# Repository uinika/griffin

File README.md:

# griffin
an evaluation PCB board with multicore CH340E ESP32 STM32 STC89C52.

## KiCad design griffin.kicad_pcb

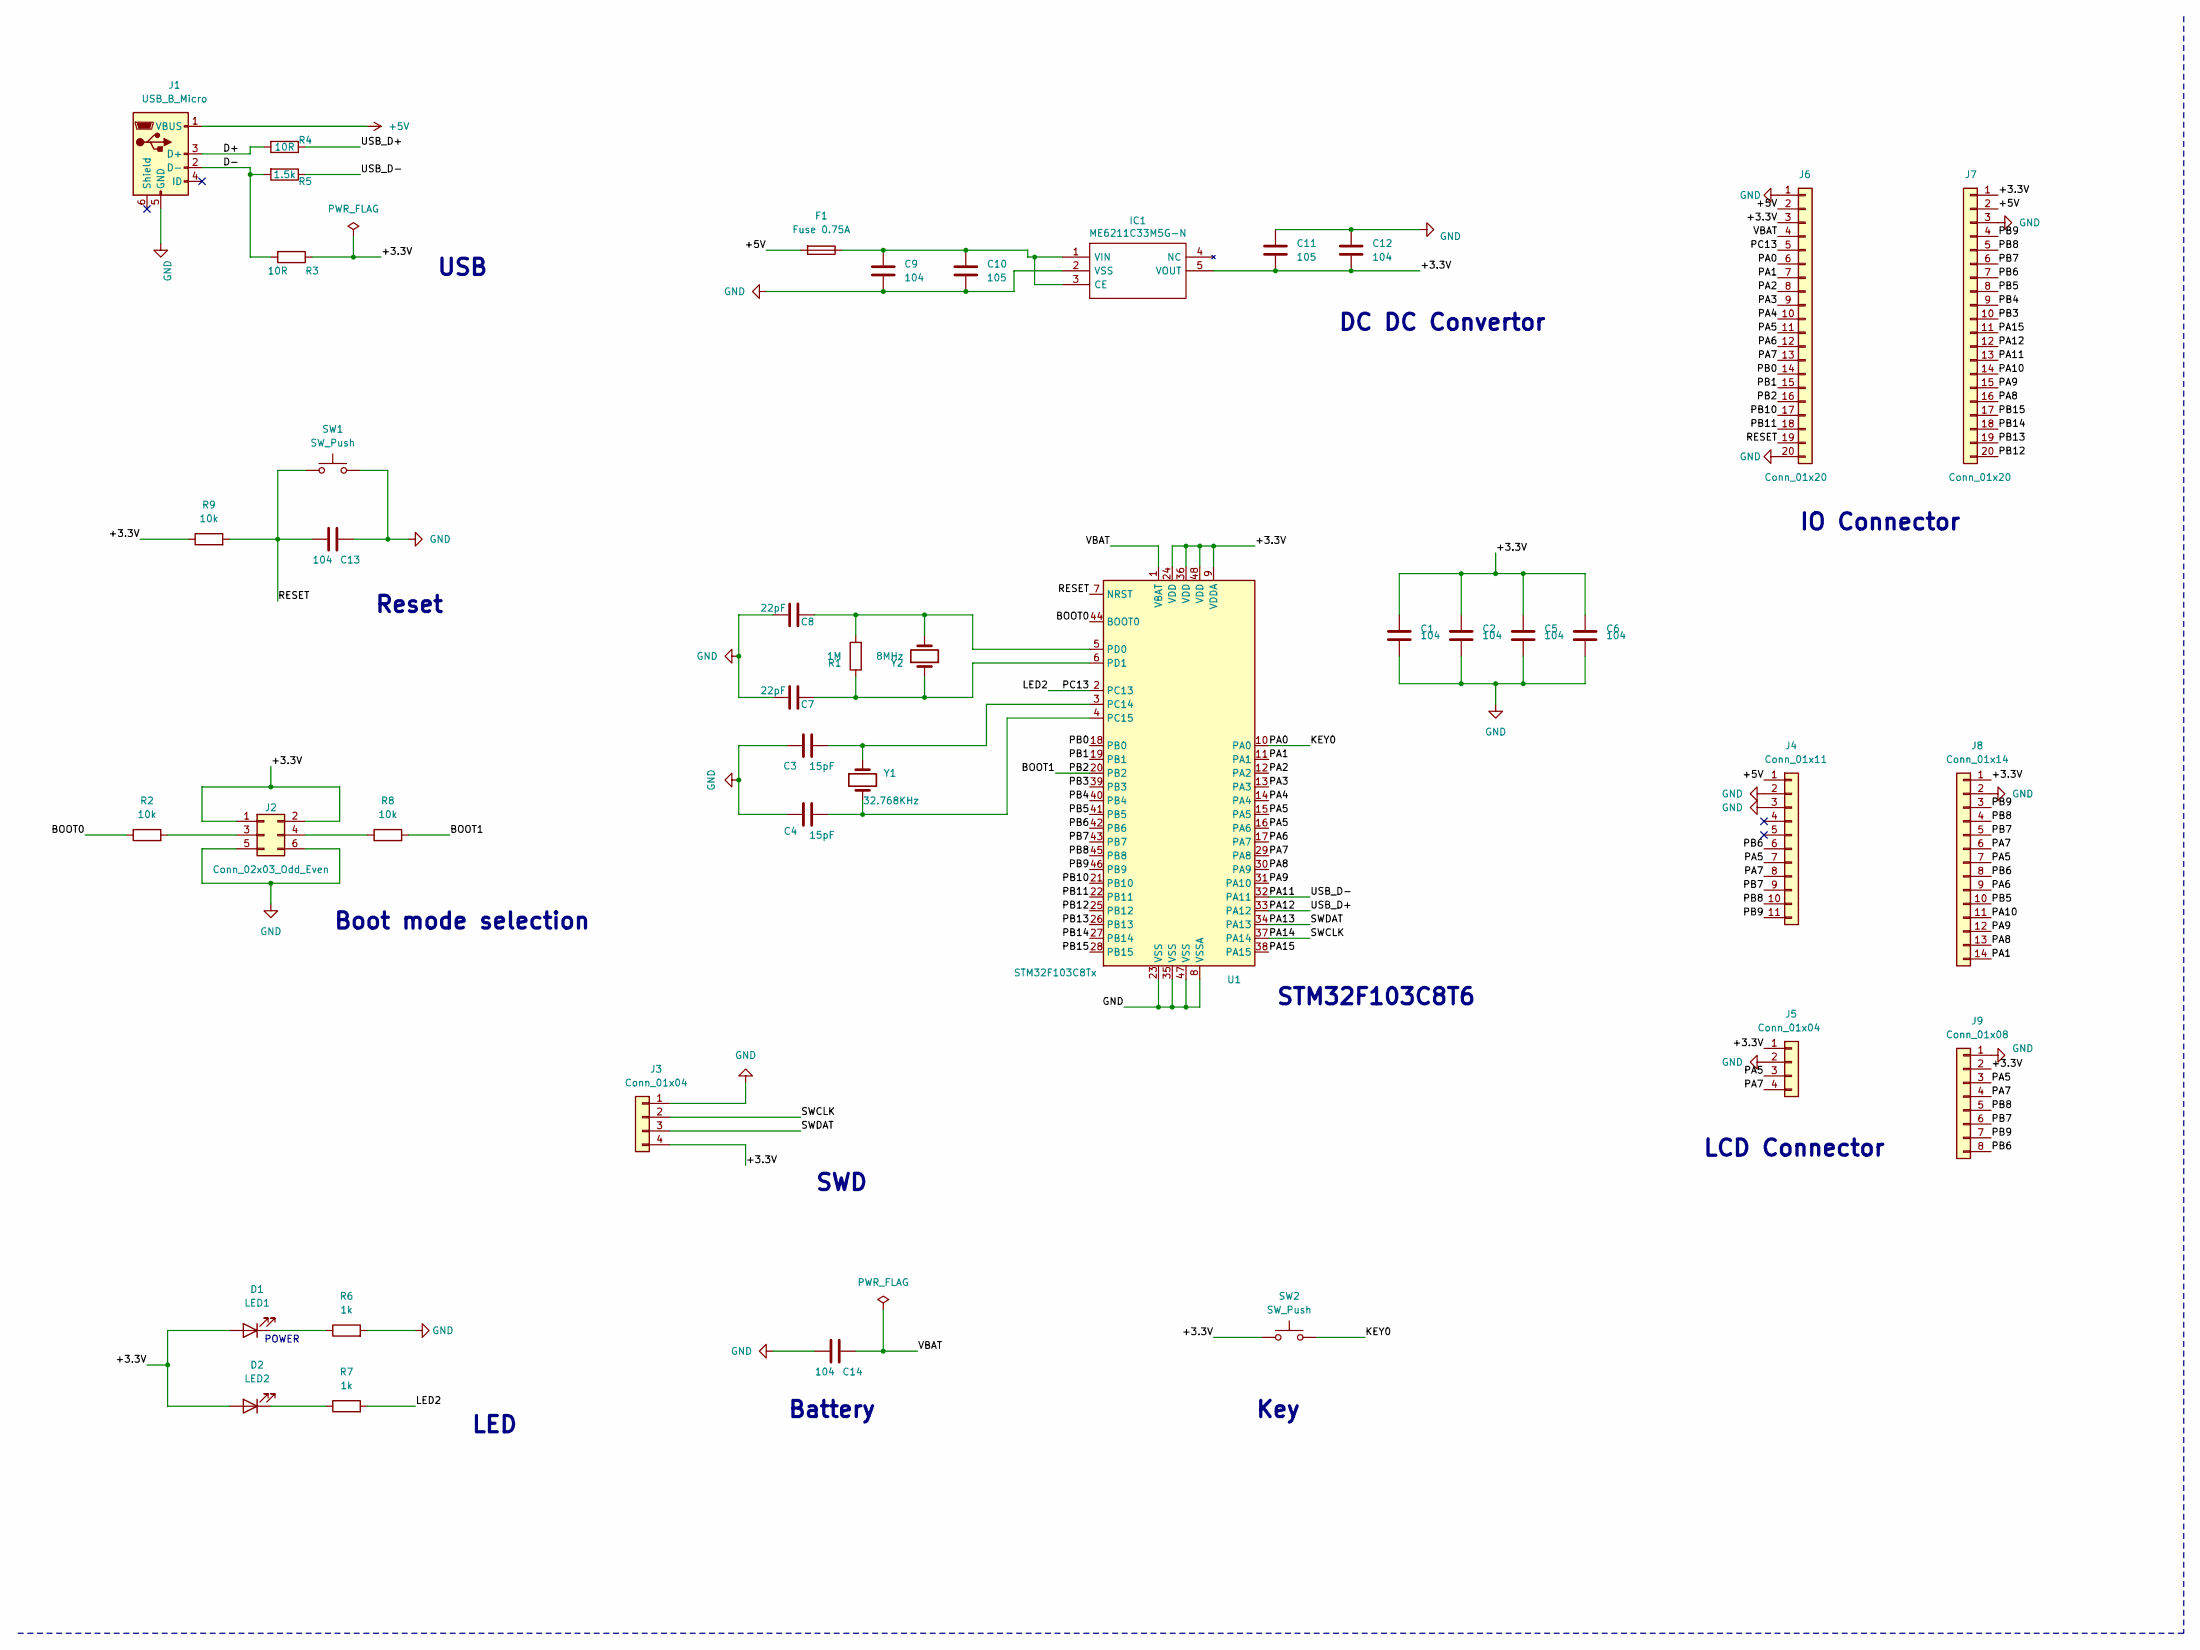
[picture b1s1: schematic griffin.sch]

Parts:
C1, C2, C5, C6, C9, C12, C13, C14: 104; C_0603_1608Metric
C3, C4: 15pF; C_0603_1608Metric
C7, C8: 22pF; C_0603_1608Metric
C10, C11: 105; C_0603_1608Metric
D1: LED1; LED_0805_2012Metric
D2: LED2; LED_0805_2012Metric
F1: Fuse 0.75A; Fuse_0805_2012Metric
IC1: ME6211C33M5G-N; SOT95P270X145-5N; Manufacturer_Part_Number ME6211C33M5G-N
J1: USB_B_Micro; USB_Micro-B_Molex-105017-0001
J2: Conn_02x03_Odd_Even; PinHeader_2x03_P2.54mm_Vertical
J3: Conn_01x04; PinSocket_1x04_P2.54mm_Vertical
J4: Conn_01x11; PinSocket_1x11_P2.54mm_Vertical
J5: Conn_01x04; PinHeader_1x04_P2.54mm_Vertical
J6, J7: Conn_01x20; PinHeader_1x20_P2.54mm_Vertical
J8: Conn_01x14; PinSocket_1x14_P2.54mm_Vertical
J9: Conn_01x08; PinSocket_1x08_P2.54mm_Vertical
R1: 1M; R_0603_1608Metric
R2, R8, R9: 10k; R_0603_1608Metric
R3, R4: 10R; R_0603_1608Metric
R5: 1.5k; R_0603_1608Metric
R6, R7: 1k; R_0603_1608Metric
SW1, SW2: SW_Push; SW_PUSH_6mm
U1: STM32F103C8Tx; LQFP-48_7x7mm_P0.5mm
Y1: 32.768KHz; Crystal_SMD_3215-2Pin_3.2x1.5mm
Y2: 8MHz; Crystal_HC18-U_Vertical

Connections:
+5V: F1.2, J1.1 (VBUS), J4.1, J6.2, J7.2
/+3.3V: C1.2, C2.2, C5.2, C6.2, C11.2, C12.2, D1.2 (A), D2.2 (A), IC1.5 (VOUT), J2.1, J2.2, J3.4, J5.1, J6.3, J7.1, J8.1, J9.2, R3.1, R9.1, SW2.1, U1.9 (VDDA), U1.24 (VDD), U1.36 (VDD), U1.48 (VDD)
/BOOT0: R2.1, U1.44 (BOOT0)
/BOOT1: J6.16, R8.2, U1.20 (PB2)
/D+: J1.3 (D+), R4.2
/D-: J1.2 (D-), R3.2, R5.2
/KEY0: J6.6, SW2.2, U1.10 (PA0)
/LED2: J6.5, R7.2, U1.2 (PC13)
/PA1: J6.7, J8.14, U1.11 (PA1)
/PA2: J6.8, U1.12 (PA2)
/PA3: J6.9, U1.13 (PA3)
/PA4: J6.10, U1.14 (PA4)
/PA5: J4.7, J5.3, J6.11, J8.7, J9.3, U1.15 (PA5), U1.16 (PA6)
/PA6: J6.12, J8.9, U1.17 (PA7)
/PA7: J4.8, J5.4, J6.13, J8.6, J9.4, U1.29 (PA8)
/PA8: J7.16, J8.13, U1.30 (PA9)
/PA9: J7.15, J8.12, U1.31 (PA10)
/PA10: J7.14, J8.11
/PA11: J7.13, R5.1, U1.32 (PA11)
/PA12: J7.12, R4.1, U1.33 (PA12)
/PA13: J3.3, U1.34 (PA13)
/PA14: J3.2, U1.37 (PA14)
/PA15: J7.11, U1.38 (PA15)
/PB0: J6.14, U1.18 (PB0)
/PB1: J6.15, U1.19 (PB1)
/PB3: J7.10, U1.39 (PB3)
/PB4: J7.9, U1.40 (PB4)
/PB5: J7.8, J8.10, U1.41 (PB5)
/PB6: J4.6, J7.7, J8.8, J9.8, U1.42 (PB6)
/PB7: J4.9, J7.6, J8.5, J9.6, U1.43 (PB7)
/PB8: J4.10, J7.5, J8.4, J9.5, U1.45 (PB8)
/PB9: J4.11, J7.4, J8.3, J9.7, U1.46 (PB9)
/PB10: J6.17, U1.21 (PB10)
/PB11: J6.18, U1.22 (PB11)
/PB12: J7.20, U1.25 (PB12)
/PB13: J7.19, U1.26 (PB13)
/PB14: J7.18, U1.27 (PB14)
/PB15: J7.17, U1.28 (PB15)
/RESET: C13.2, J6.19, R9.2, SW1.1, U1.7 (NRST)
/VBAT: C14.1, J6.4, U1.1 (VBAT)
GND: C1.1, C2.1, C3.1, C4.1, C5.1, C6.1, C7.1, C8.1, C9.2, C10.2, C11.1, C12.1, C13.1, C14.2, IC1.2 (VSS), J1.5 (GND), J2.5, J2.6, J3.1, J4.2, J4.3, J5.2, J6.1, J6.20, J7.3, J8.2, J9.1, R6.2, SW1.2, U1.8 (VSSA), U1.23 (VSS), U1.35 (VSS), U1.47 (VSS)
unnamed: C3.2, U1.3 (PC14), Y1.1
unnamed: C4.2, U1.4 (PC15), Y1.2
unnamed: C7.2, R1.1, U1.6 (PD1), Y2.1
unnamed: C8.2, R1.2, U1.5 (PD0), Y2.2
unnamed: C9.1, C10.1, F1.1, IC1.1 (VIN), IC1.3 (CE)
unnamed: D1.1 (K), R6.1
unnamed: D2.1 (K), R7.1
unnamed: J2.3, R2.2
unnamed: J2.4, R8.1

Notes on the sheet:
STM32F103C8T6
DC DC Convertor
LED
Boot mode selection
SWD
LCD Connector
IO Connector
Battery
Key
Reset
POWER
USB

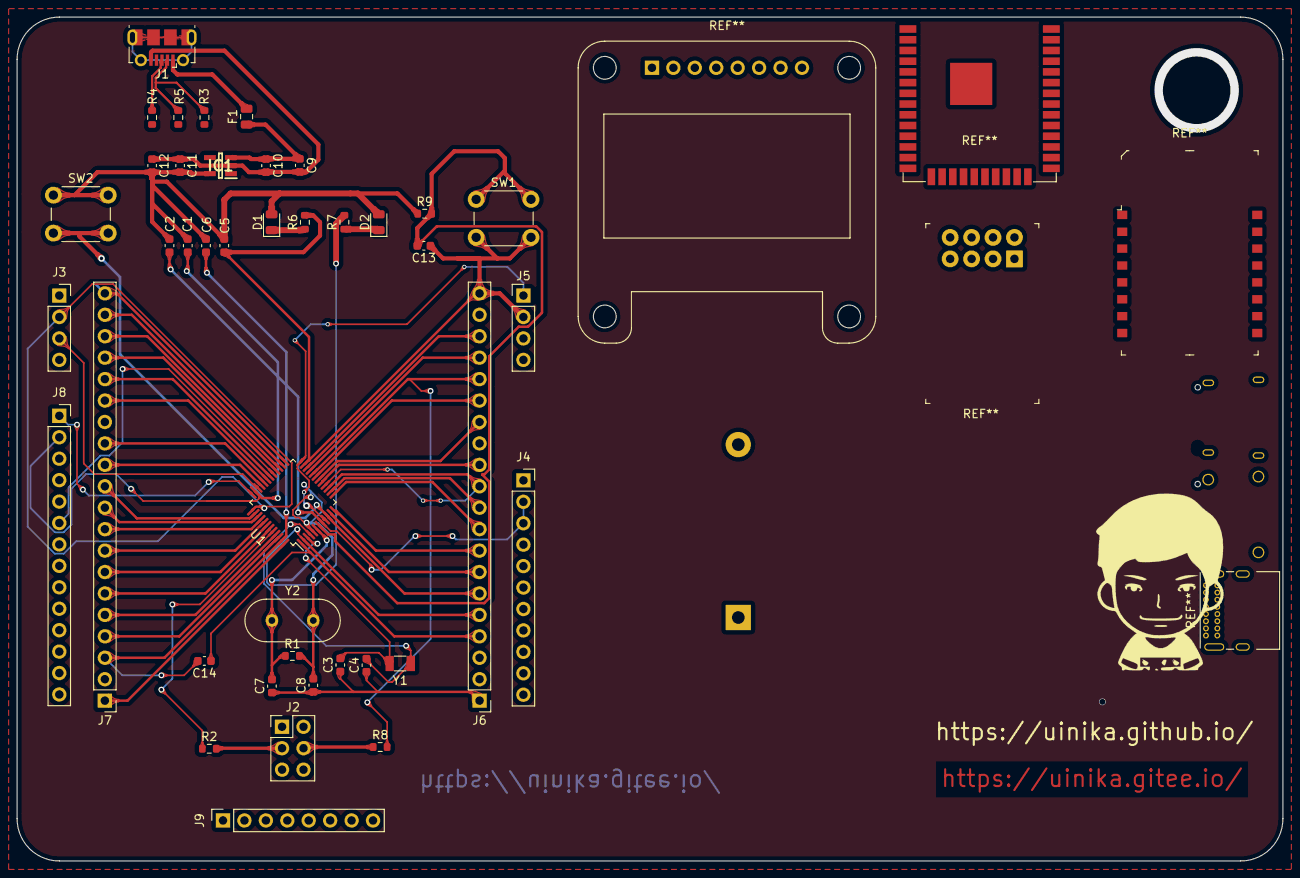
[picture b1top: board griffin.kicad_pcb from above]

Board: 2 copper layers, 150.0 x 100.0 mm, 42 parts (1 on the bottom side), 50 nets.

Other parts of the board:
hank: LOGO; hank-silk

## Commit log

2021-02-25 initialize schematic and edge.
2021-03-23 schematic for STM32F103C8T6
2021-03-25 resize height & width for PCB
2021-03-25 update schematic diagram
2021-03-26 support borad margin
2021-03-26 update PCB
2021-03-26 remove _autosave-griffin.sch from .gitignore
2021-03-26 adjust symbole libraries
2021-03-26 Add cabling rules
2021-03-29 finish PCB layout
2021-03-30 generate gerber files
